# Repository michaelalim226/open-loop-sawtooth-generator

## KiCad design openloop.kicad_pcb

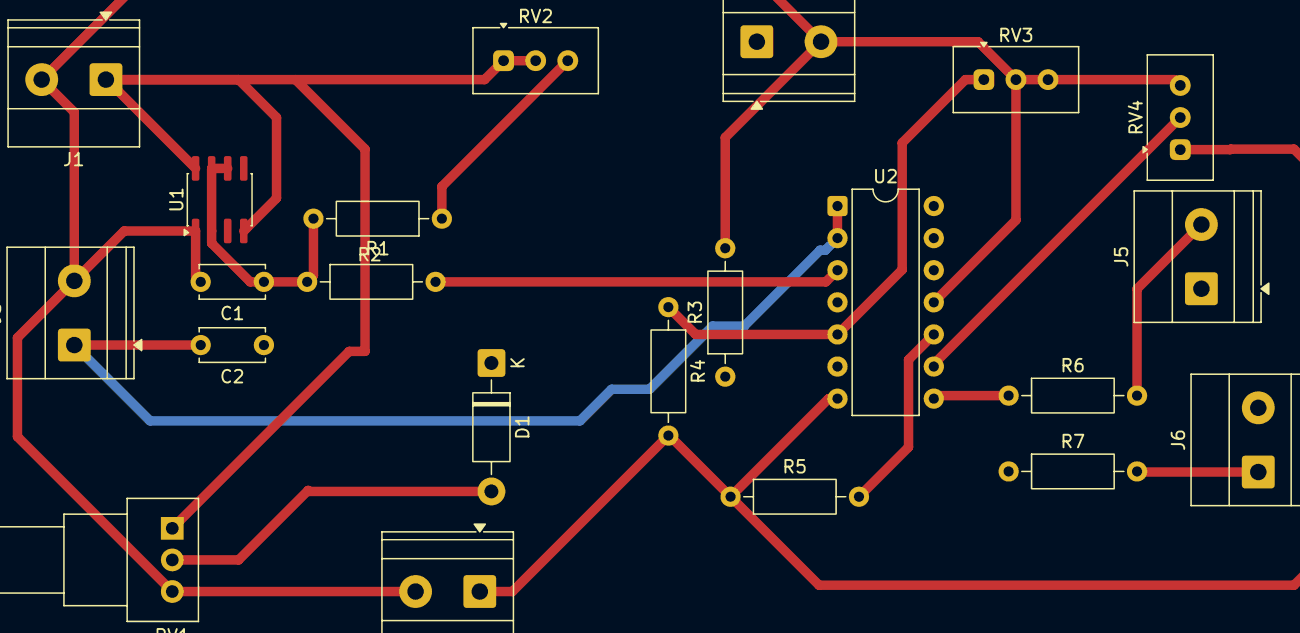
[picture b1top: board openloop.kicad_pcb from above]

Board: 2 copper layers, 22 parts (0 on the bottom side), 15 nets.

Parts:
C1, C2: C; C_Disc_D5.0mm_W2.5mm_P5.00mm
D1: 1N4007; D_DO-41_SOD81_P10.16mm_Horizontal
J1, J2, J3, J4, J5, J6: Screw_Terminal_01x02; TerminalBlock_Phoenix_MKDS-1,5-2-5.08_1x02_P5.08mm_Horizont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
R1, R2, R3, R4, R5, R6, R7: R; R_Axial_DIN0207_L6.3mm_D2.5mm_P10.16mm_Horizontal
RV1: R_Potentiometer; Potentiometer_Alps_RK09Y11_Single_Horizontal
RV2, RV3, RV4: R_Potentiometer; Potentiometer_Vishay_T93YA_Vertical
U1: NE555D; SOIC-8_3.9x4.9mm_P1.27mm
U2: LM324; DIP-14_W7.62mm

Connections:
+5V: J1.1, RV1.1, RV2.1, RV2.2, U1.4 (R), U1.8 (VCC)
+9V: J2.1, U2.4 (V+)
GND: C1.2, J1.2, J2.2, J3.2, J4.2, J5.2, R3.2, R6.2, RV1.3, RV3.2, RV3.3, RV4.3, U1.1 (GND), U2.11 (V-)
unnamed: D1.2 (A), RV1.2
unnamed: C2.1, D1.1 (K), R3.1, U2.6 (-)
unnamed: C2.2, J3.1, U2.1, U2.2 (-)
unnamed: J4.1, R4.2, R5.1, RV4.1, U2.7
unnamed: J5.1, R6.1, R7.1, U2.8
unnamed: J6.1, R7.2
unnamed: R1.1, RV2.3
unnamed: C1.1, R1.2, R2.1, U1.2 (TR), U1.6 (THR), U1.7 (DIS)
unnamed: R2.2, U2.3 (+)
unnamed: R4.1, RV3.1, U2.5 (+)
unnamed: R5.2, U2.10 (+)
unnamed: RV4.2, U2.9 (-)
